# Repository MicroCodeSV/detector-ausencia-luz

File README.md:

# detector-ausencia-luz
Tarjeta de circuito empleada en el taller soldadura y revelado

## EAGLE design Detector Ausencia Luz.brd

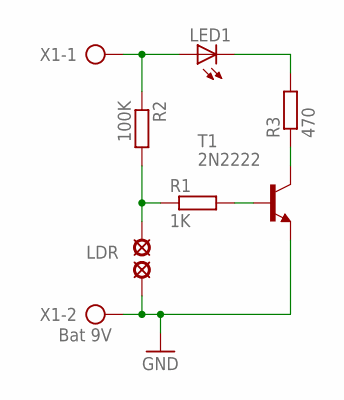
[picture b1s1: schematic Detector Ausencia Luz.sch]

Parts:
LED1: LED5MM
LSP1, LSP2: SE11
R1: 1K; 0207/10
R2: 100K; 0207/10
R3: 470; 0207/10
T1: 2N2222; TO92-CBE
X1: Bat 9V; AK500/2

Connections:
GND: LSP2.MP, T1.E, X1.2
unnamed: R1.2, T1.B
unnamed: LED1.A, R2.1, X1.1
unnamed: LSP1.MP, R1.1, R2.2
unnamed: R3.1, T1.C
unnamed: LED1.K (C), R3.2

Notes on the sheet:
LDR

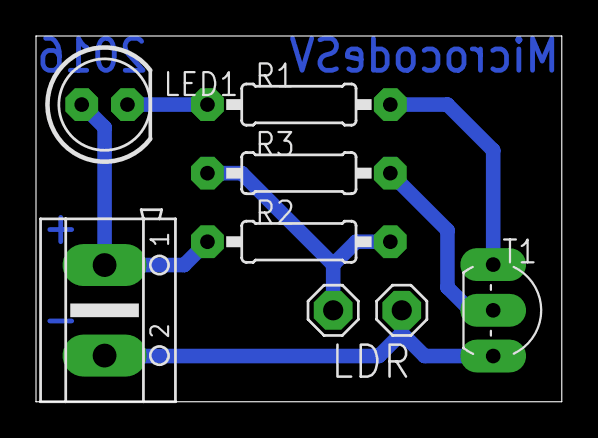
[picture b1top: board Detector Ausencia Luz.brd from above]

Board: 2 copper layers, 29.2 x 20.3 mm, 8 parts (0 on the bottom side), 6 nets.

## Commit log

2016-08-22 Subidos los archivos al repositorio
2016-10-26 Creando el readme
